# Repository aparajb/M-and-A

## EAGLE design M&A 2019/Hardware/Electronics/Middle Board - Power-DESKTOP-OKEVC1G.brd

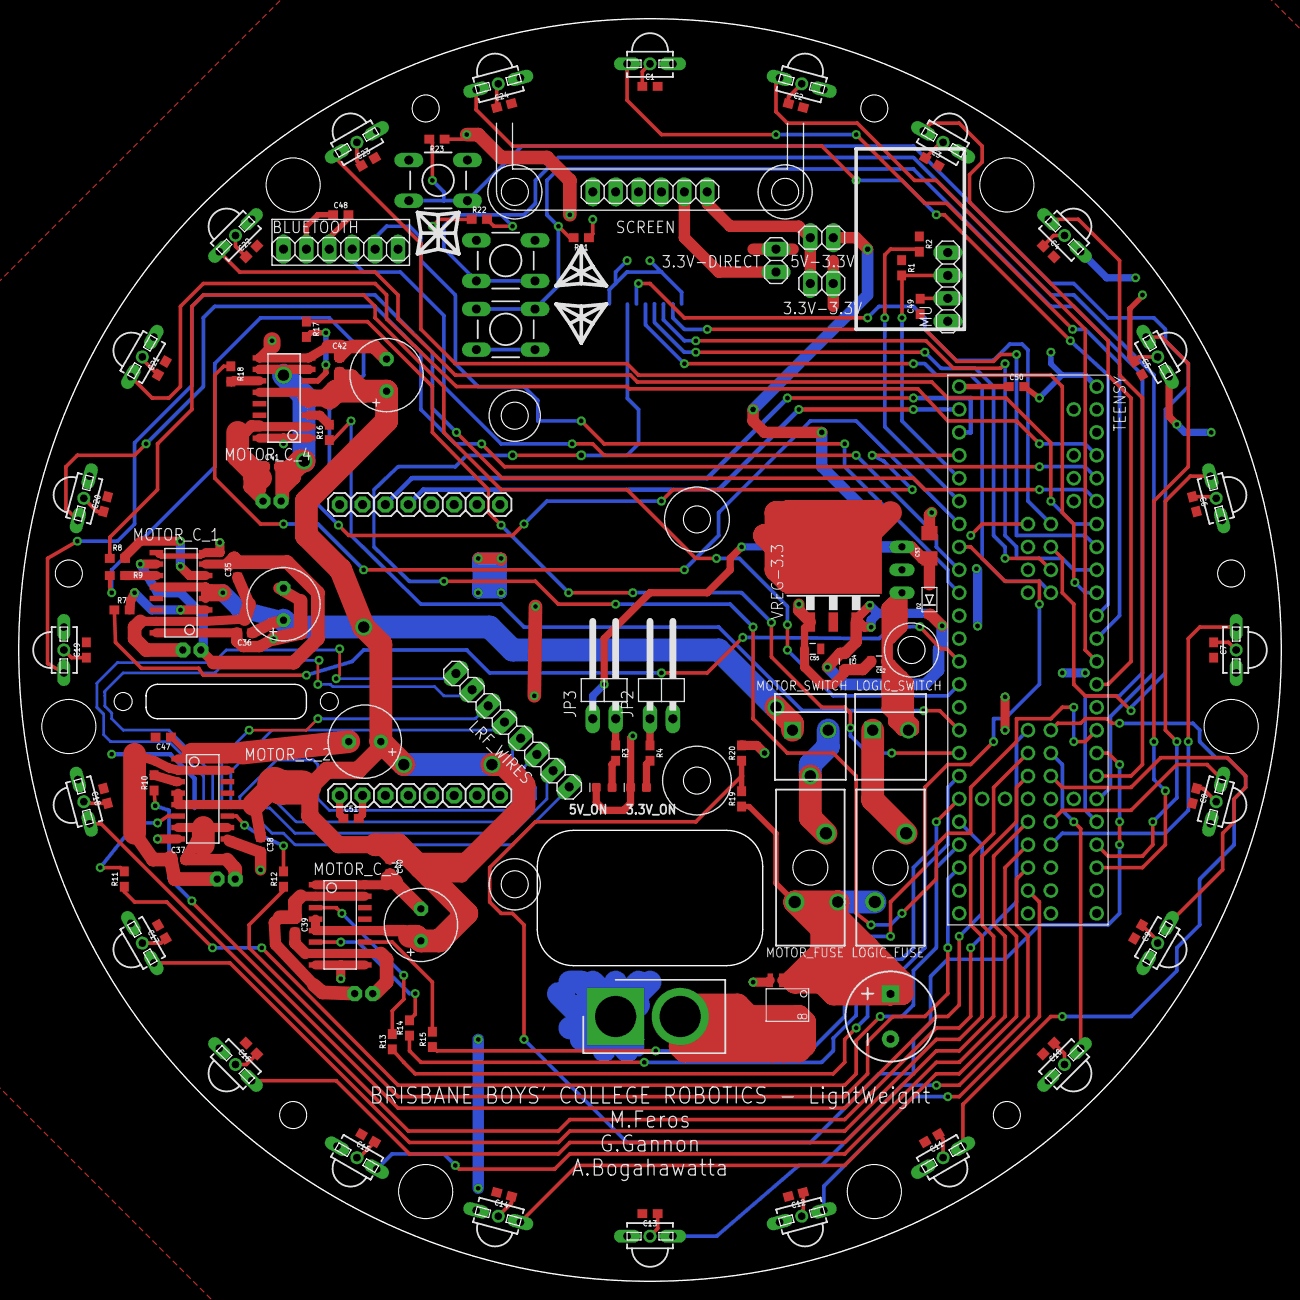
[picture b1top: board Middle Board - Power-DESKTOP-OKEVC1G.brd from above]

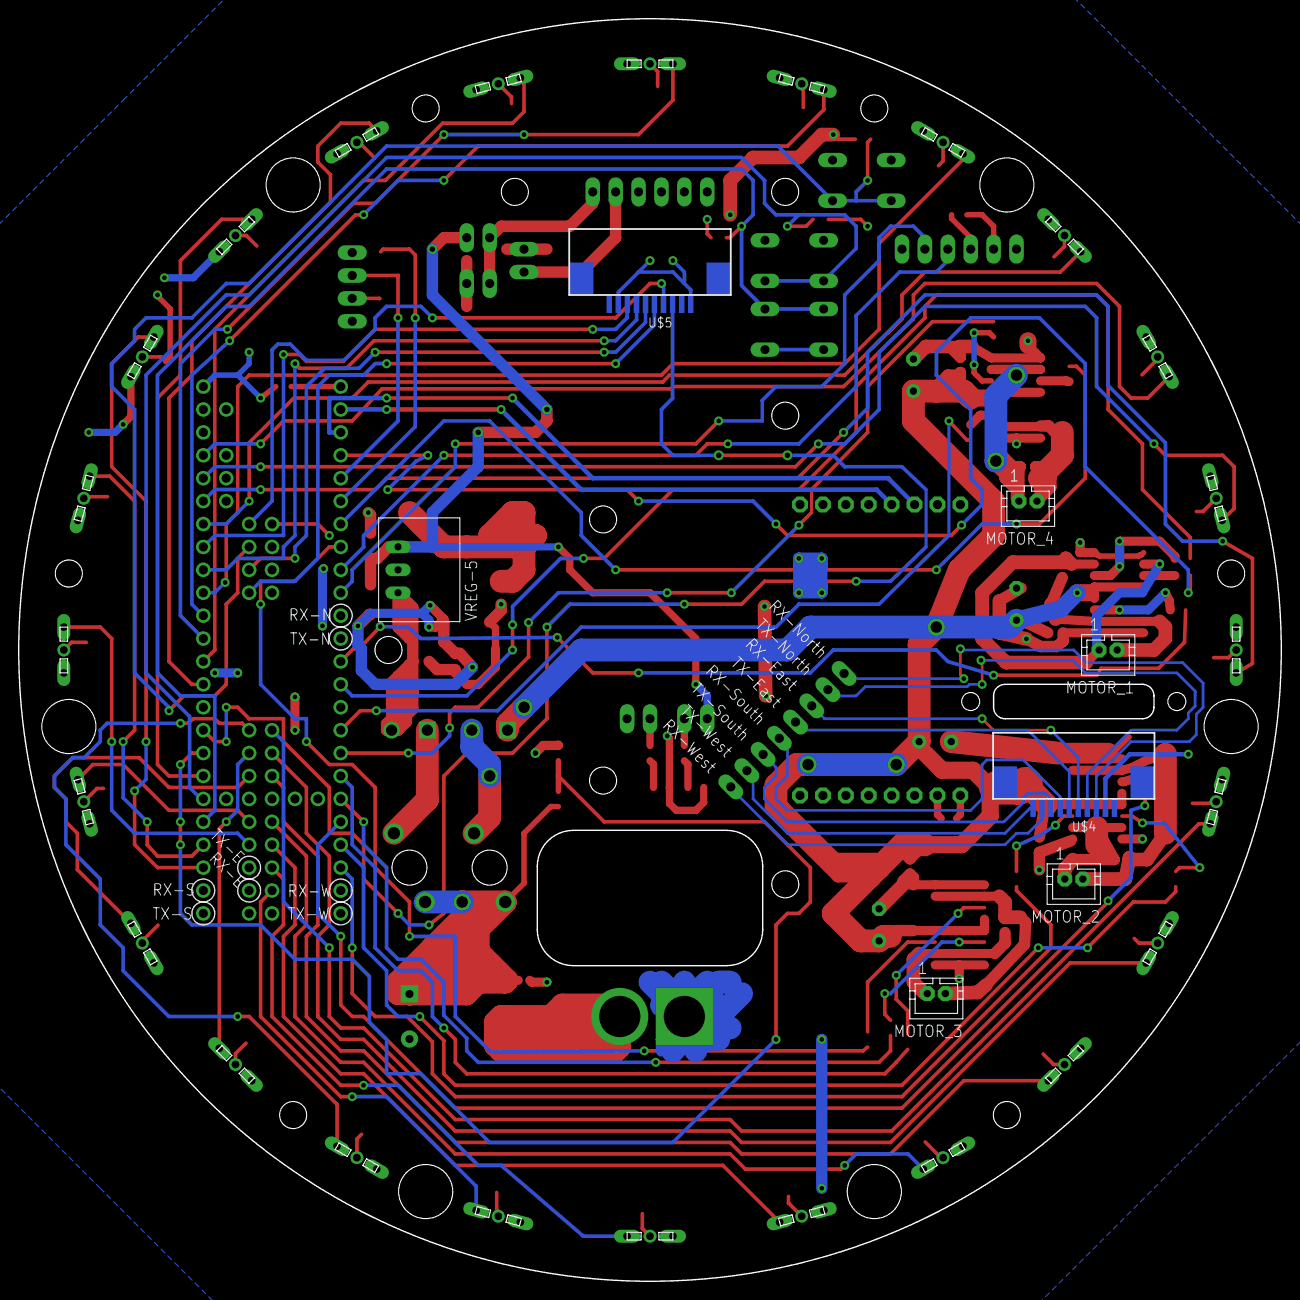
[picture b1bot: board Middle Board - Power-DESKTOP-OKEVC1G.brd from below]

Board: 2 copper layers, 140.0 x 140.0 mm, 126 parts (7 on the bottom side), 96 nets.

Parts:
3.3V-3.3V, 3.3V-DIRECT, 5V-3.3V: 1X02
3.3V_ON, 5V_ON: GREEN; LED-0603
BLUETOOTH: 1X06
C1, C2, C3, C4, C5, C6, C7, C8, C9, C10, C11, C12, C13, C14, C15, C16, C17, C18, C19, C20, C21, C22, C23, C24, C35, C36, C37, C38, C39, C40, C41, C42, C47, C48, C49, C50, C51: 0.1uF; 0603
C25: 1mF; CPOL-RADIAL-5MM-10MM
C43, C44, C45, C46: 470uF; E3,5-8
C52, C54, C55: 10uF; SPARKFUN-CAPACITORS_0805
C53: 22uF; SPARKFUN-CAPACITORS_1206
D2: ADAFRUIT_SOD-123FL
DOWN: DTS-6
IMU: 1X04
J1: PRT-10474; SHDR2W320P716_1X2_1574X813X158
JP2, JP3: 1X02/90
LOGIC_FUSE: FUSE_MINI_BLADE; SL-1538
LOGIC_SWITCH: CONN_02_JST-VH; B2P-VH
LRF_WIRES: 1X08
MOTOR_1, MOTOR_2, MOTOR_3, MOTOR_4: JST-PH2
MOTOR_C_1, MOTOR_C_2, MOTOR_C_3, MOTOR_C_4: VNH7100BASTR; SO-16
MOTOR_FUSE: FUSE_MINI_BLADE; SL-1538
MOTOR_SWITCH: CONN_02_JST-VH; B2P-VH
OPEN-MV: OPENMV3
R1, R2, R21, R22, R23: 10k; 0603
R3, R4: 680; 0603
R7, R8, R9, R10, R11, R12, R13, R14, R15, R16, R17, R18: 1k; 0603
R19: 35.7kOhm; 0603
R20: 10.2kOhm; 0603
SCREEN: 1X06
SELECT: DTS-6
TEENSY: TEENSY-3.5
TSSP1, TSSP2, TSSP3, TSSP4, TSSP5, TSSP6, TSSP7, TSSP8, TSSP9, TSSP10, TSSP11, TSSP12, TSSP13, TSSP14, TSSP15, TSSP16, TSSP17, TSSP18, TSSP19, TSSP20, TSSP21, TSSP22, TSSP23, TSSP24: TSSP58038; MINICAST
U$2: SI4143DY; SO-8
U$4, U$5: FPC10
UP: DTS-6
VREG-3.3: LINEAR_LM340S-05; LINEAR_TO263-3
VREG-5: V78-2000-SWITCHING-REGULATOR_V78-2000

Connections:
3.3V: 3.3V-3.3V.1, 3.3V-DIRECT.1, BLUETOOTH.2, C1.2, C2.2, C3.2, C4.2, C5.2, C6.2, C7.2, C8.2, C9.2, C10.2, C11.2, C12.2, C13.2, C14.2, C15.2, C16.2, C17.2, C18.2, C19.2, C20.2, C21.2, C22.2, C23.2, C24.2, C47.2, C48.1, C49.1, C50.2, C51.2, C55.1, DOWN.1, DOWN.2, IMU.1, JP2.2, OPEN-MV.27, R1.1, R2.1, SELECT.1, SELECT.2, TEENSY.VIN, TSSP1.1, TSSP2.1, TSSP3.1, TSSP4.1, TSSP5.1, TSSP6.1, TSSP7.1, TSSP8.1, TSSP9.1, TSSP10.1, TSSP11.1, TSSP12.1, TSSP13.1, TSSP14.1, TSSP15.1, TSSP16.1, TSSP17.1, TSSP18.1, TSSP19.1, TSSP20.1, TSSP21.1, TSSP22.1, TSSP23.1, TSSP24.1, U$4.2, U$5.1, U$5.9, UP.1, UP.2, VREG-3.3.2, VREG-3.3.TAB
3.3V_ON: JP2.1, R4.1
5V: 5V-3.3V.1, C53.1, D2.A, JP3.1, VREG-5.3
5V-ON: JP3.2, R3.1
12V: C36.1, C38.1, C40.1, C42.1, C43.+, C44.+, C45.+, C46.+, MOTOR_C_1.4, MOTOR_C_1.5, MOTOR_C_1.12, MOTOR_C_2.4, MOTOR_C_2.5, MOTOR_C_2.12, MOTOR_C_3.4, MOTOR_C_3.5, MOTOR_C_3.12, MOTOR_C_4.4, MOTOR_C_4.5, MOTOR_C_4.12, MOTOR_SWITCH.1
BATTERY-VOLTAGE(ANALOG): R19.2, R20.1, TEENSY.DA0
BDOWN: DOWN.3, DOWN.4, R22.2, TEENSY.38
BSELECT: R23.2, SELECT.3, SELECT.4, TEENSY.56
BUP: R21.2, TEENSY.37, UP.3, UP.4
GND: 3.3V_ON.C, 5V_ON.C, BLUETOOTH.3, C1.1, C2.1, C3.1, C4.1, C5.1, C6.1, C7.1, C8.1, C9.1, C10.1, C11.1, C12.1, C13.1, C14.1, C15.1, C16.1, C17.1, C18.1, C19.1, C20.1, C21.1, C22.1, C23.1, C24.1, C25.-, C36.2, C38.2, C40.2, C42.2, C43.-, C44.-, C45.-, C46.-, C47.1, C48.2, C49.2, C50.1, C51.1, C52.2, C53.2, C54.2, C55.2, IMU.2, J1.1, MOTOR_C_1.1, MOTOR_C_1.8, MOTOR_C_1.9, MOTOR_C_1.16, MOTOR_C_2.1, MOTOR_C_2.8, MOTOR_C_2.9, MOTOR_C_2.16, MOTOR_C_3.1, MOTOR_C_3.8, MOTOR_C_3.9, MOTOR_C_3.16, MOTOR_C_4.1, MOTOR_C_4.8, MOTOR_C_4.9, MOTOR_C_4.16, OPEN-MV.28, R20.2, R21.1, R22.1, R23.1, SCREEN.4, TEENSY.GND, TEENSY.GND-2, TEENSY.GND-3, TEENSY.GND-4, TSSP1.2, TSSP2.2, TSSP3.2, TSSP4.2, TSSP5.2, TSSP6.2, TSSP7.2, TSSP8.2, TSSP9.2, TSSP10.2, TSSP11.2, TSSP12.2, TSSP13.2, TSSP14.2, TSSP15.2, TSSP16.2, TSSP17.2, TSSP18.2, TSSP19.2, TSSP20.2, TSSP21.2, TSSP22.2, TSSP23.2, TSSP24.2, U$2.4, U$4.1, U$5.2, U$5.10, VREG-3.3.1, VREG-5.2
LS-CONTROL1: TEENSY.19, U$5.8
LS-CONTROL2: TEENSY.18, U$5.7
LS-CONTROL3: TEENSY.55, U$5.6
LS-CONTROL4: TEENSY.54, U$5.5
LS-CONTROL5: TEENSY.57, U$5.4
LS-OUTPUT: TEENSY.DA1, U$5.3
MOTOR-BL(ENA): R16.1, TEENSY.24
MOTOR-BL(ENB): R17.1, TEENSY.25
MOTOR-BL(PWM): R18.1, TEENSY.5
MOTOR-BR(ENA): R13.1, TEENSY.26
MOTOR-BR(ENB): R14.1, TEENSY.27
MOTOR-BR(PWM): R15.1, TEENSY.6
MOTOR-FL(ENA): R7.1, TEENSY.11
MOTOR-FL(ENB): R8.1, TEENSY.12
MOTOR-FL(PWM): R9.1, TEENSY.2
MOTOR-FR(ENA): R10.1, TEENSY.28
MOTOR-FR(ENB): R11.1, TEENSY.29
MOTOR-FR(PWM): R12.1, TEENSY.30
unnamed: J1.2, U$2.5, U$2.6, U$2.7, U$2.8
unnamed: MOTOR_FUSE.P$2, MOTOR_SWITCH.2
unnamed: C25.+, LOGIC_FUSE.P$1, MOTOR_FUSE.P$1, R19.1, U$2.1, U$2.2, U$2.3
unnamed: LOGIC_FUSE.P$2, LOGIC_SWITCH.1
unnamed: MOTOR_C_1.3, R7.2
unnamed: 5V_ON.A, R3.2
unnamed: 3.3V_ON.A, R4.2
unnamed: MOTOR_C_1.6, R8.2
unnamed: MOTOR_C_1.11, R9.2
unnamed: C35.1, MOTOR_1.2, MOTOR_C_1.2, MOTOR_C_1.15
unnamed: C35.2, MOTOR_1.1, MOTOR_C_1.7, MOTOR_C_1.10
unnamed: MOTOR_C_2.3, R10.2
unnamed: MOTOR_C_2.6, R11.2
unnamed: MOTOR_C_2.11, R12.2
unnamed: C37.1, MOTOR_2.2, MOTOR_C_2.2, MOTOR_C_2.15
unnamed: C37.2, MOTOR_2.1, MOTOR_C_2.7, MOTOR_C_2.10
unnamed: MOTOR_C_3.3, R13.2
unnamed: MOTOR_C_3.6, R14.2
unnamed: MOTOR_C_3.11, R15.2
unnamed: C39.1, MOTOR_3.2, MOTOR_C_3.2, MOTOR_C_3.15
unnamed: C39.2, MOTOR_3.1, MOTOR_C_3.7, MOTOR_C_3.10
unnamed: MOTOR_C_4.3, R16.2
unnamed: MOTOR_C_4.6, R17.2
unnamed: MOTOR_C_4.11, R18.2
unnamed: C41.1, MOTOR_4.2, MOTOR_C_4.2, MOTOR_C_4.15
unnamed: C41.2, MOTOR_4.1, MOTOR_C_4.7, MOTOR_C_4.10
unnamed: 3.3V-DIRECT.2, SCREEN.5
unnamed: 3.3V-3.3V.2, 5V-3.3V.2, SCREEN.6
unnamed: C52.1, LOGIC_SWITCH.2, VREG-5.1
unnamed: C54.1, D2.C, VREG-3.3.3
RX(BLUETOOTH): BLUETOOTH.5, TEENSY.8
RX(CAM): OPEN-MV.16, TEENSY.1
RXE: LRF_WIRES.6, U$4.5
RXN: LRF_WIRES.8, U$4.3
RXS: LRF_WIRES.4, U$4.7
RXW: LRF_WIRES.1, U$4.9
SCL(IMU): IMU.3, R1.2, TEENSY.3
SDA(IMU): IMU.4, R2.2, TEENSY.4
TSSP1: TEENSY.15, TSSP1.3
TSSP2: TEENSY.14, TSSP2.3
TSSP3: TEENSY.13, TSSP3.3
TSSP4: TEENSY.39, TSSP4.3
TSSP5: TEENSY.35, TSSP5.3
TSSP6: TEENSY.36, TSSP6.3
TSSP7: TEENSY.49, TSSP7.3
TSSP8: TEENSY.50, TSSP8.3
TSSP9: TEENSY.51, TSSP9.3
TSSP10: TEENSY.52, TSSP10.3
TSSP11: TEENSY.53, TSSP11.3
TSSP12: TEENSY.46, TSSP12.3
TSSP13: TEENSY.45, TSSP13.3
TSSP14: TEENSY.44, TSSP14.3
TSSP15: TEENSY.43, TSSP15.3
TSSP16: TEENSY.42, TSSP16.3
TSSP17: TEENSY.41, TSSP17.3
TSSP18: TEENSY.40, TSSP18.3
TSSP19: TEENSY.21, TSSP19.3
TSSP20: TEENSY.22, TSSP20.3
TSSP21: TEENSY.23, TSSP21.3
TSSP22: TEENSY.20, TSSP22.3
TSSP23: TEENSY.17, TSSP23.3
TSSP24: TEENSY.16, TSSP24.3
TX(BLUETOOTH): BLUETOOTH.4, TEENSY.7
TX(CAM): OPEN-MV.15, TEENSY.0
TXE: LRF_WIRES.5, U$4.6
TXN: LRF_WIRES.7, U$4.4
TXS: LRF_WIRES.3, U$4.8
TXW: LRF_WIRES.2, U$4.10

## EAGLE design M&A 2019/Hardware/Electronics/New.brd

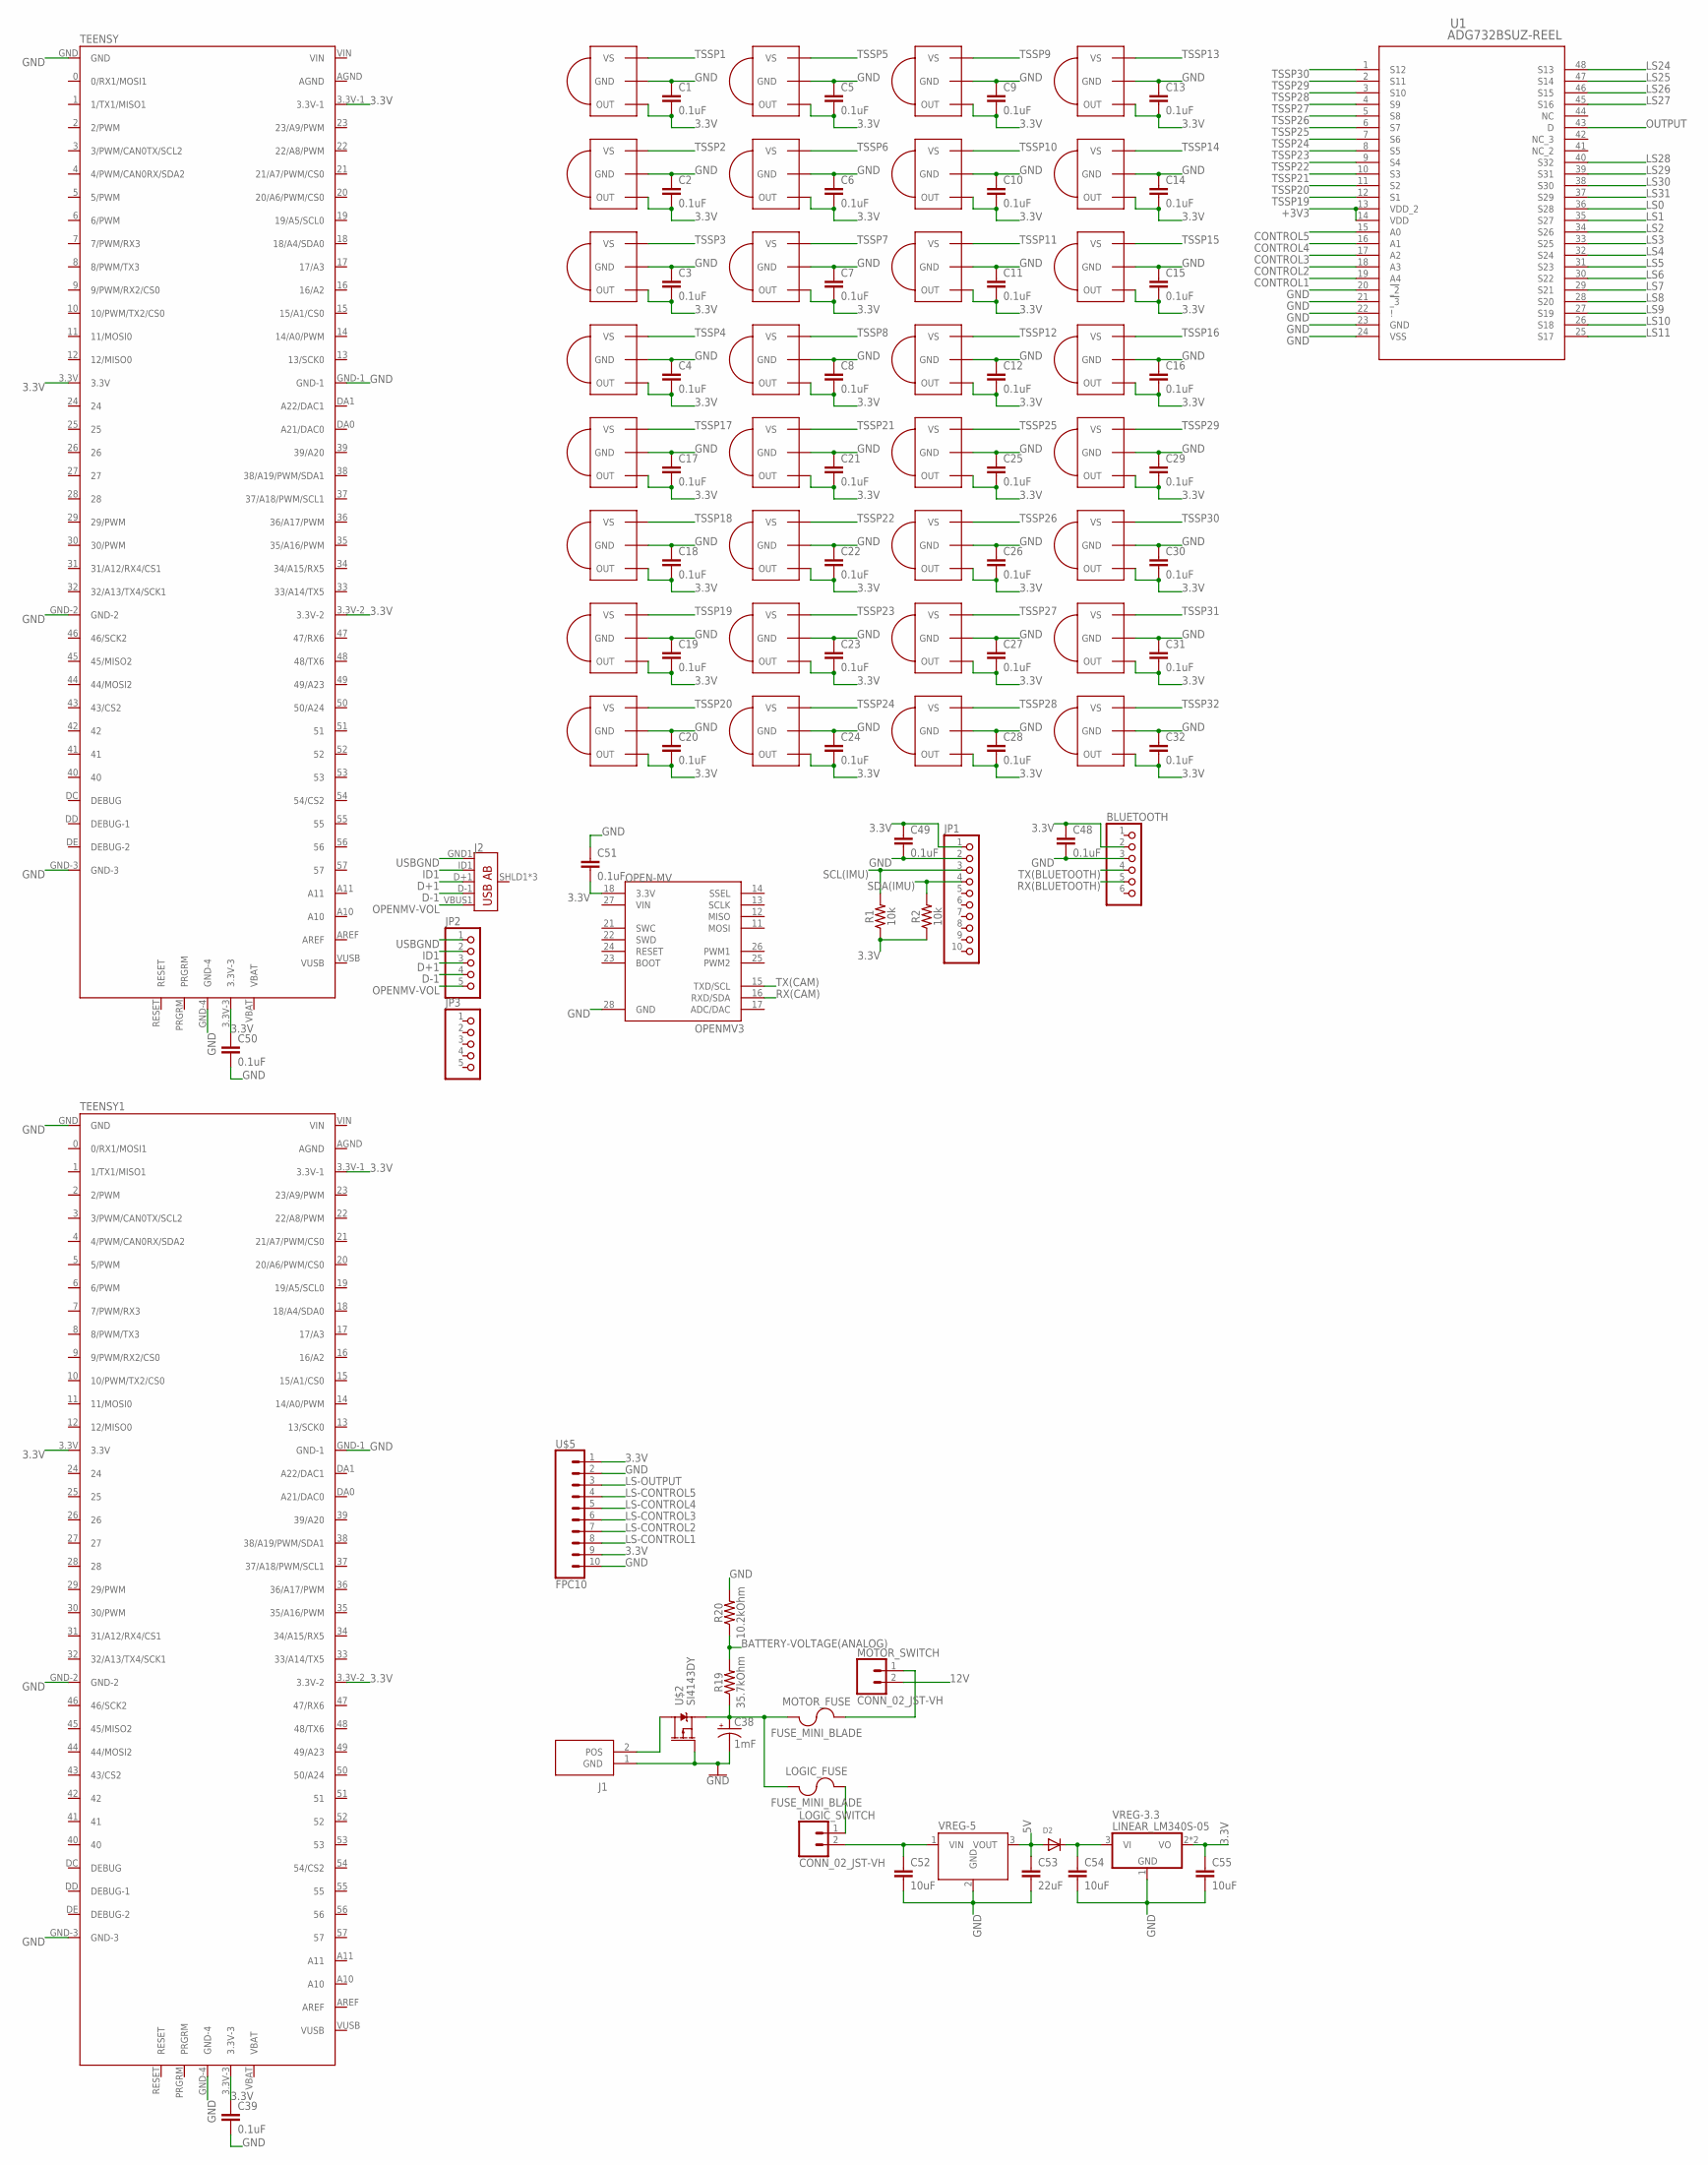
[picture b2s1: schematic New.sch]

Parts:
BLUETOOTH: PINHD-1X6; 1X06
C1, C2, C3, C4, C5, C6, C7, C8, C9, C10, C11, C12, C13, C14, C15, C16, C17, C18, C19, C20, C21, C22, C23, C24, C25, C26, C27, C28, C29, C30, C31, C32, C39, C48, C49, C50, C51: 0.1uF; 0603
C38: 1mF; CPOL-RADIAL-5MM-10MM
C52, C54, C55: 10uF; SPARKFUN-CAPACITORS_0805
C53: 22uF; SPARKFUN-CAPACITORS_1206
D2: ADAFRUIT_DIODE_SOD-123FL:1; ADAFRUIT_SOD-123FL
J1: PRT-10474; SHDR2W320P716_1X2_1574X813X158
J2: USB_AB_SMT; USB-AB-MICRO-SMD
JP1: PINHD-1X10; 1X10
JP2, JP3: PINHD-1X5; 1X05
LOGIC_FUSE: FUSE_MINI_BLADE; SL-1538
LOGIC_SWITCH: CONN_02_JST-VH; B2P-VH@1
MOTOR_FUSE: FUSE_MINI_BLADE; SL-1538
MOTOR_SWITCH: CONN_02_JST-VH; B2P-VH@1
OPEN-MV: OPENMV3
R1, R2: 10k; 0603
R19: 35.7kOhm; 0603
R20: 10.2kOhm; 0603
TEENSY, TEENSY1: TEENSY-3.5
TSSP1, TSSP2, TSSP3, TSSP4, TSSP5, TSSP6, TSSP7, TSSP8, TSSP9, TSSP10, TSSP11, TSSP12, TSSP13, TSSP14, TSSP15, TSSP16, TSSP17, TSSP18, TSSP19, TSSP20, TSSP21, TSSP22, TSSP23, TSSP24, TSSP25, TSSP26, TSSP27, TSSP28, TSSP29, TSSP30, TSSP31, TSSP32: TSSP58038; MINICAST
U1: ADG732BSUZ-REEL; SU_48
U$2: SI4143DY; SO-8
U$5: FPC10
VREG-3.3: LINEAR_LM340S-05; LINEAR_TO263-3
VREG-5: V78-2000-SWITCHING-REGULATOR_V78-2000

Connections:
3.3V: BLUETOOTH.2, C1.2, C2.2, C3.2, C4.2, C5.2, C6.2, C7.2, C8.2, C9.2, C10.2, C11.2, C12.2, C13.2, C14.2, C15.2, C16.2, C17.2, C18.2, C19.2, C20.2, C21.2, C22.2, C23.2, C24.2, C25.2, C26.2, C27.2, C28.2, C29.2, C30.2, C31.2, C32.2, C39.1, C48.1, C49.1, C50.1, C51.2, C55.1, JP1.1, OPEN-MV.18 (3.3V), R1.1, R2.1, TEENSY.3.3V, TEENSY.3.3V-1, TEENSY.3.3V-2, TEENSY.3.3V-3, TEENSY1.3.3V, TEENSY1.3.3V-1, TEENSY1.3.3V-2, TEENSY1.3.3V-3, TSSP1.1 (OUT), TSSP2.1 (OUT), TSSP3.1 (OUT), TSSP4.1 (OUT), TSSP5.1 (OUT), TSSP6.1 (OUT), TSSP7.1 (OUT), TSSP8.1 (OUT), TSSP9.1 (OUT), TSSP10.1 (OUT), TSSP11.1 (OUT), TSSP12.1 (OUT), TSSP13.1 (OUT), TSSP14.1 (OUT), TSSP15.1 (OUT), TSSP16.1 (OUT), TSSP17.1 (OUT), TSSP18.1 (OUT), TSSP19.1 (OUT), TSSP20.1 (OUT), TSSP21.1 (OUT), TSSP22.1 (OUT), TSSP23.1 (OUT), TSSP24.1 (OUT), TSSP25.1 (OUT), TSSP26.1 (OUT), TSSP27.1 (OUT), TSSP28.1 (OUT), TSSP29.1 (OUT), TSSP30.1 (OUT), TSSP31.1 (OUT), TSSP32.1 (OUT), U$5.1, U$5.9, VREG-3.3.2 (VO), VREG-3.3.TAB (VO)
5V: C53.1, D2.A, VREG-5.3 (VOUT)
12V: MOTOR_SWITCH.2
+3V3: U1.13 (VDD_2), U1.14 (VDD)
BATTERY-VOLTAGE(ANALOG): R19.2, R20.1
CONTROL1: U1.19 (A4)
CONTROL2: U1.18 (A3)
CONTROL3: U1.17 (A2)
CONTROL4: U1.16 (A1)
CONTROL5: U1.15 (A0)
D+1: J2.D+1 (D+), JP2.3
D-1: J2.D-1 (D-), JP2.4
GND: BLUETOOTH.3, C1.1, C2.1, C3.1, C4.1, C5.1, C6.1, C7.1, C8.1, C9.1, C10.1, C11.1, C12.1, C13.1, C14.1, C15.1, C16.1, C17.1, C18.1, C19.1, C20.1, C21.1, C22.1, C23.1, C24.1, C25.1, C26.1, C27.1, C28.1, C29.1, C30.1, C31.1, C32.1, C38.-, C39.2, C48.2, C49.2, C50.2, C51.1, C52.2, C53.2, C54.2, C55.2, J1.1 (GND), JP1.2, OPEN-MV.28 (GND), R20.2, TEENSY.GND, TEENSY.GND-1, TEENSY.GND-2, TEENSY.GND-3, TEENSY.GND-4, TEENSY1.GND, TEENSY1.GND-1, TEENSY1.GND-2, TEENSY1.GND-3, TEENSY1.GND-4, TSSP1.2 (GND), TSSP2.2 (GND), TSSP3.2 (GND), TSSP4.2 (GND), TSSP5.2 (GND), TSSP6.2 (GND), TSSP7.2 (GND), TSSP8.2 (GND), TSSP9.2 (GND), TSSP10.2 (GND), TSSP11.2 (GND), TSSP12.2 (GND), TSSP13.2 (GND), TSSP14.2 (GND), TSSP15.2 (GND), TSSP16.2 (GND), TSSP17.2 (GND), TSSP18.2 (GND), TSSP19.2 (GND), TSSP20.2 (GND), TSSP21.2 (GND), TSSP22.2 (GND), TSSP23.2 (GND), TSSP24.2 (GND), TSSP25.2 (GND), TSSP26.2 (GND), TSSP27.2 (GND), TSSP28.2 (GND), TSSP29.2 (GND), TSSP30.2 (GND), TSSP31.2 (GND), TSSP32.2 (GND), U1.20 (!_2), U1.21 (!_3), U1.22 (!), U1.23 (GND), U1.24 (VSS), U$2.4 (G), U$5.2, U$5.10, VREG-3.3.1 (GND), VREG-5.2 (GND)
ID1: J2.ID1 (USBID), JP2.2
LS0: U1.36 (S28)
LS1: U1.35 (S27)
LS2: U1.34 (S26)
LS3: U1.33 (S25)
LS4: U1.32 (S24)
LS5: U1.31 (S23)
LS6: U1.30 (S22)
LS7: U1.29 (S21)
LS8: U1.28 (S20)
LS9: U1.27 (S19)
LS10: U1.26 (S18)
LS11: U1.25 (S17)
LS24: U1.48 (S13)
LS25: U1.47 (S14)
LS26: U1.46 (S15)
LS27: U1.45 (S16)
LS28: U1.40 (S32)
LS29: U1.39 (S31)
LS30: U1.38 (S30)
LS31: U1.37 (S29)
LS-CONTROL1: U$5.8
LS-CONTROL2: U$5.7
LS-CONTROL3: U$5.6
LS-CONTROL4: U$5.5
LS-CONTROL5: U$5.4
LS-OUTPUT: U$5.3
unnamed: J1.2 (POS), U$2.5 (D), U$2.6 (D), U$2.7 (D), U$2.8 (D)
unnamed: MOTOR_FUSE.P$2 (2), MOTOR_SWITCH.1
unnamed: C38.+, LOGIC_FUSE.P$1 (1), MOTOR_FUSE.P$1 (1), R19.1, U$2.1 (S), U$2.2 (S), U$2.3 (S)
unnamed: LOGIC_FUSE.P$2 (2), LOGIC_SWITCH.1
unnamed: C52.1, LOGIC_SWITCH.2, VREG-5.1 (VIN)
unnamed: C54.1, D2.C, VREG-3.3.3 (VI)
OPENMV-VOL: J2.VBUS1 (VBUS), JP2.5
OUTPUT: U1.43 (D)
RX(BLUETOOTH): BLUETOOTH.5
RX(CAM): OPEN-MV.16 (RXD/SDA)
SCL(IMU): JP1.3, R1.2
SDA(IMU): JP1.4, R2.2
TSSP1: TSSP1.3 (VS)
TSSP2: TSSP2.3 (VS)
TSSP3: TSSP3.3 (VS)
TSSP4: TSSP4.3 (VS)
TSSP5: TSSP5.3 (VS)
TSSP6: TSSP6.3 (VS)
TSSP7: TSSP7.3 (VS)
TSSP8: TSSP8.3 (VS)
TSSP9: TSSP9.3 (VS)
TSSP10: TSSP10.3 (VS)
TSSP11: TSSP11.3 (VS)
TSSP12: TSSP12.3 (VS)
TSSP13: TSSP13.3 (VS)
TSSP14: TSSP14.3 (VS)
TSSP15: TSSP15.3 (VS)
TSSP16: TSSP16.3 (VS)
TSSP17: TSSP17.3 (VS)
TSSP18: TSSP18.3 (VS)
TSSP19: TSSP19.3 (VS), U1.12 (S1)
TSSP20: TSSP20.3 (VS), U1.11 (S2)
TSSP21: TSSP21.3 (VS), U1.10 (S3)
TSSP22: TSSP22.3 (VS), U1.9 (S4)
TSSP23: TSSP23.3 (VS), U1.8 (S5)
TSSP24: TSSP24.3 (VS), U1.7 (S6)
TSSP25: TSSP25.3 (VS), U1.6 (S7)
TSSP26: TSSP26.3 (VS), U1.5 (S8)
TSSP27: TSSP27.3 (VS), U1.4 (S9)
TSSP28: TSSP28.3 (VS), U1.3 (S10)
TSSP29: TSSP29.3 (VS), U1.2 (S11)
TSSP30: TSSP30.3 (VS), U1.1 (S12)
TSSP31: TSSP31.3 (VS)
TSSP32: TSSP32.3 (VS)
TX(BLUETOOTH): BLUETOOTH.4
TX(CAM): OPEN-MV.15 (TXD/SCL)
USBGND: J2.GND1 (GND), JP2.1
VIN: OPEN-MV.27 (VIN)

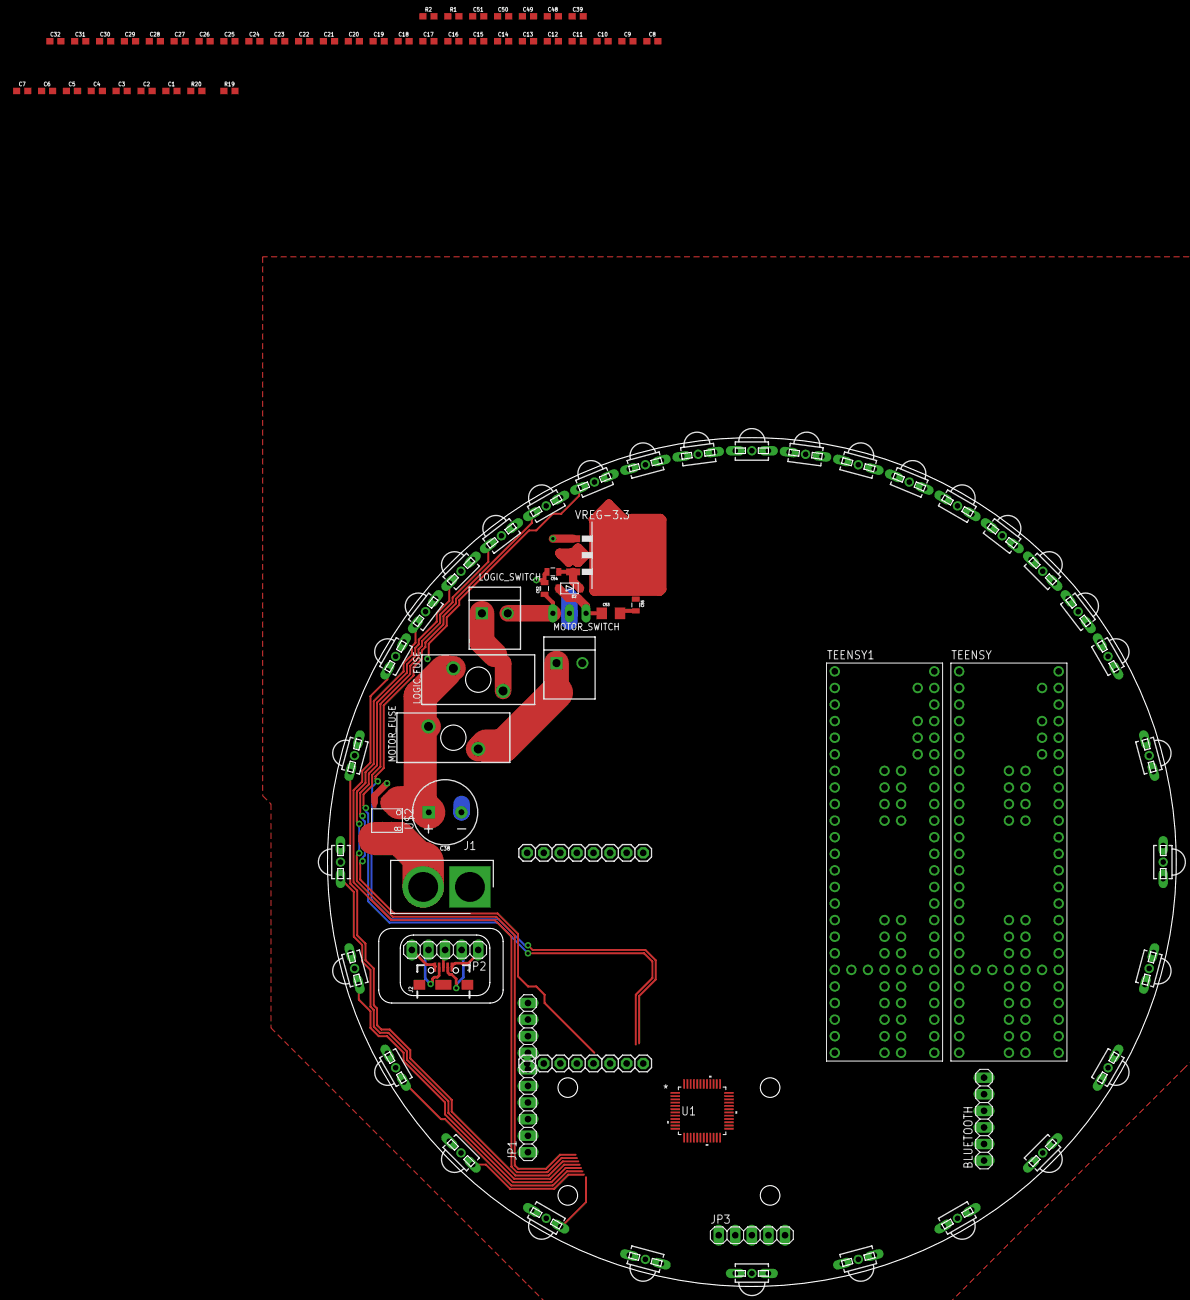
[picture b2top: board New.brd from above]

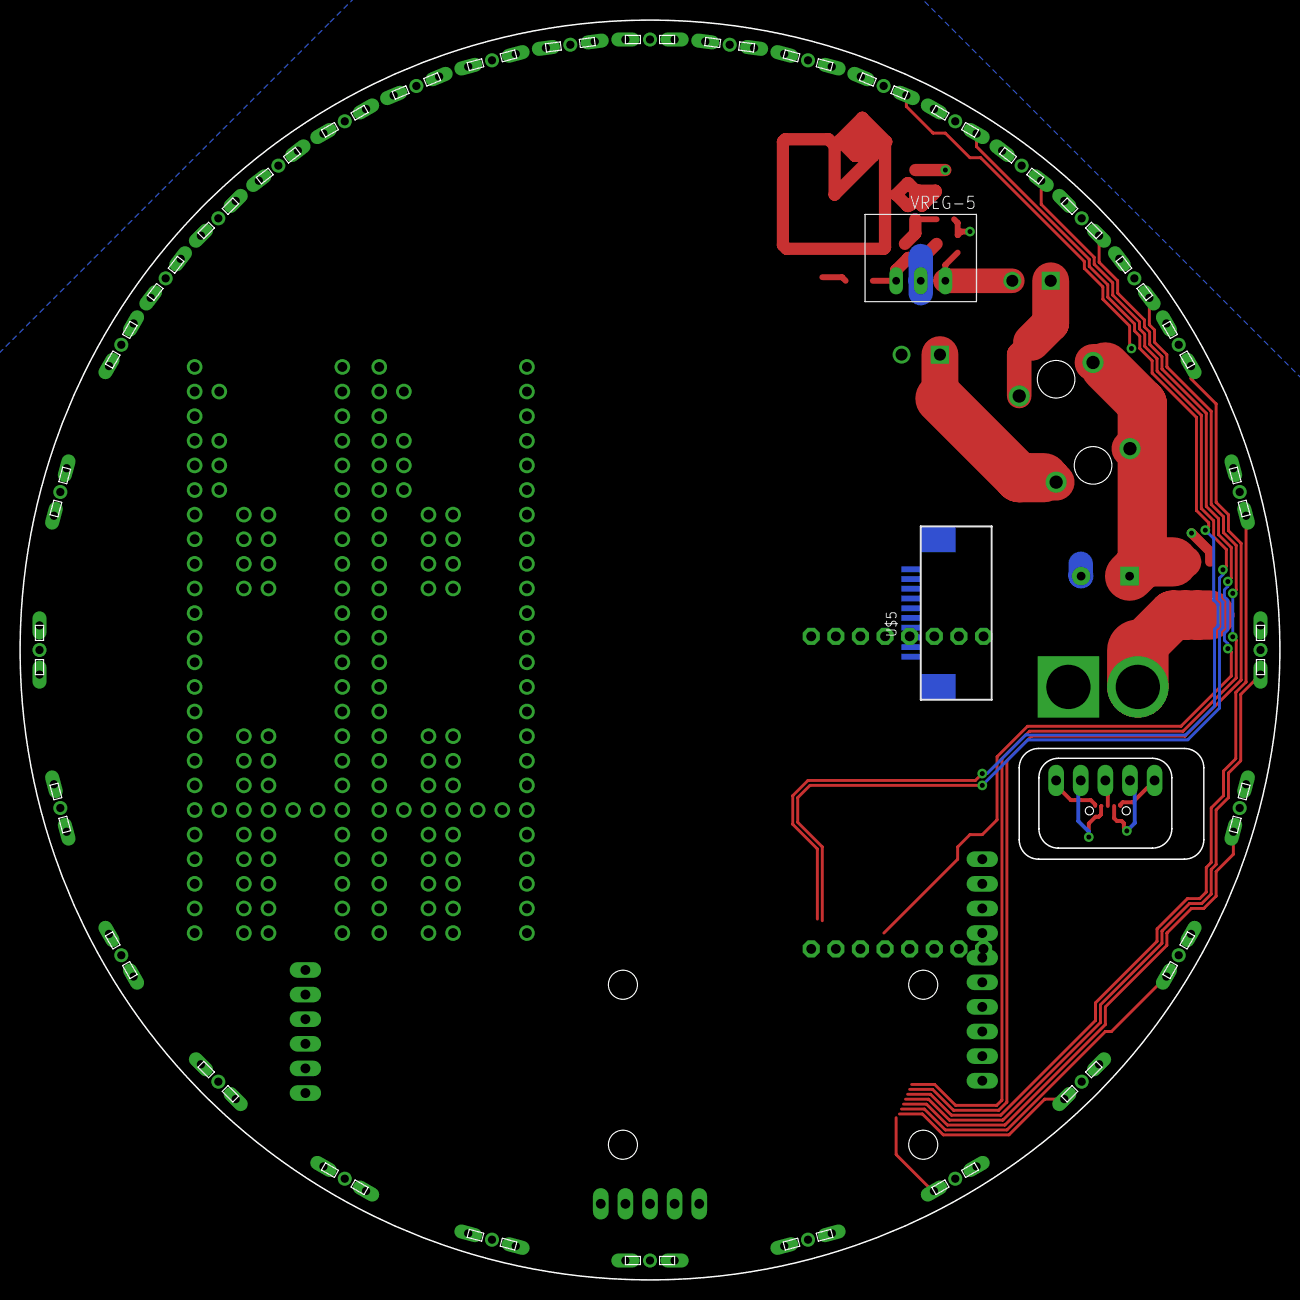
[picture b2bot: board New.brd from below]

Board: 2 copper layers, 130.0 x 130.0 mm, 97 parts (2 on the bottom side), 30 nets.

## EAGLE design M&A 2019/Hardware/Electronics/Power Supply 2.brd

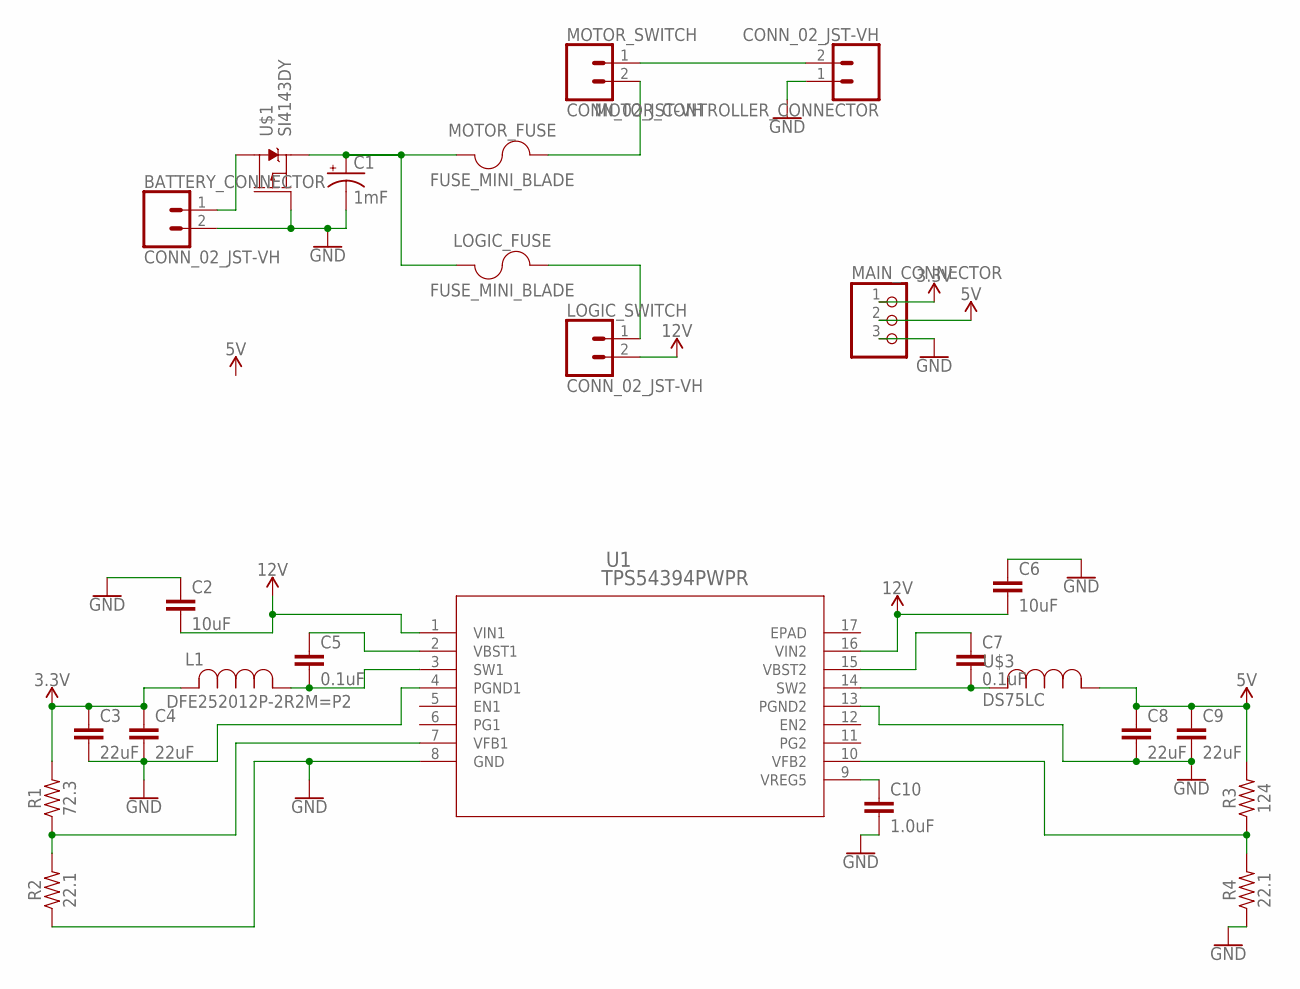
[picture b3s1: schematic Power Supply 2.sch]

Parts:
BATTERY_CONNECTOR: CONN_02_JST-VH; B2P-VH
C1: 1mF; CPOL-RADIAL-5MM-10MM
C2, C6: 10uF; 0805
C3, C4, C8, C9: 22uF; 0805
C5, C7: 0.1uF; 0603
C10: 1.0uF; 0805
L1: DFE252012P-2R2M=P2; DFE252012P-1R0M=P2
LOGIC_FUSE: FUSE_MINI_BLADE; SL-1538
LOGIC_SWITCH: CONN_02_JST-VH; B2P-VH
MAIN_CONNECTOR: PINHD-1X3; 1X03
MOTOR_CONTROLLER_CONNECTOR: CONN_02_JST-VH; B2P-VH
MOTOR_FUSE: FUSE_MINI_BLADE; SL-1538
MOTOR_SWITCH: CONN_02_JST-VH; B2P-VH
R1: 72.3; 0603
R2, R4: 22.1; 0603
R3: 124; 0603
U1: TPS54394PWPR; PWP16_3P4X2P46
U$1: SI4143DY; SO-8
U$3: DS75LC

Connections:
3.3V: C3.1, C4.1, L1.2, MAIN_CONNECTOR.1, R1.2
5V: C8.1, C9.1, MAIN_CONNECTOR.2, R3.2, U$3.P$1 (1)
12V: C2.2, C6.2, LOGIC_SWITCH.2, U1.1 (VIN1), U1.16 (VIN2)
GND: BATTERY_CONNECTOR.2, C1.-, C2.1, C3.2, C4.2, C6.1, C8.2, C9.2, C10.2, MAIN_CONNECTOR.3, MOTOR_CONTROLLER_CONNECTOR.1, R2.1, R4.1, U1.4 (PGND1), U1.8 (GND), U1.13 (PGND2), U$1.4 (G)
unnamed: BATTERY_CONNECTOR.1, U$1.5 (D), U$1.6 (D), U$1.7 (D), U$1.8 (D)
unnamed: MOTOR_FUSE.P$2 (2), MOTOR_SWITCH.2
unnamed: C1.+, LOGIC_FUSE.P$1 (1), MOTOR_FUSE.P$1 (1), U$1.1 (S), U$1.2 (S), U$1.3 (S)
unnamed: LOGIC_FUSE.P$2 (2), LOGIC_SWITCH.1
unnamed: MOTOR_CONTROLLER_CONNECTOR.2, MOTOR_SWITCH.1
unnamed: C5.1, U1.2 (VBST1)
unnamed: C5.2, L1.1, U1.3 (SW1)
unnamed: C7.1, U1.15 (VBST2)
unnamed: R1.1, R2.2, U1.7 (VFB1)
unnamed: C7.2, U1.14 (SW2), U$3.P$2 (2)
unnamed: C10.1, U1.9 (VREG5)
unnamed: R3.1, R4.2, U1.10 (VFB2)

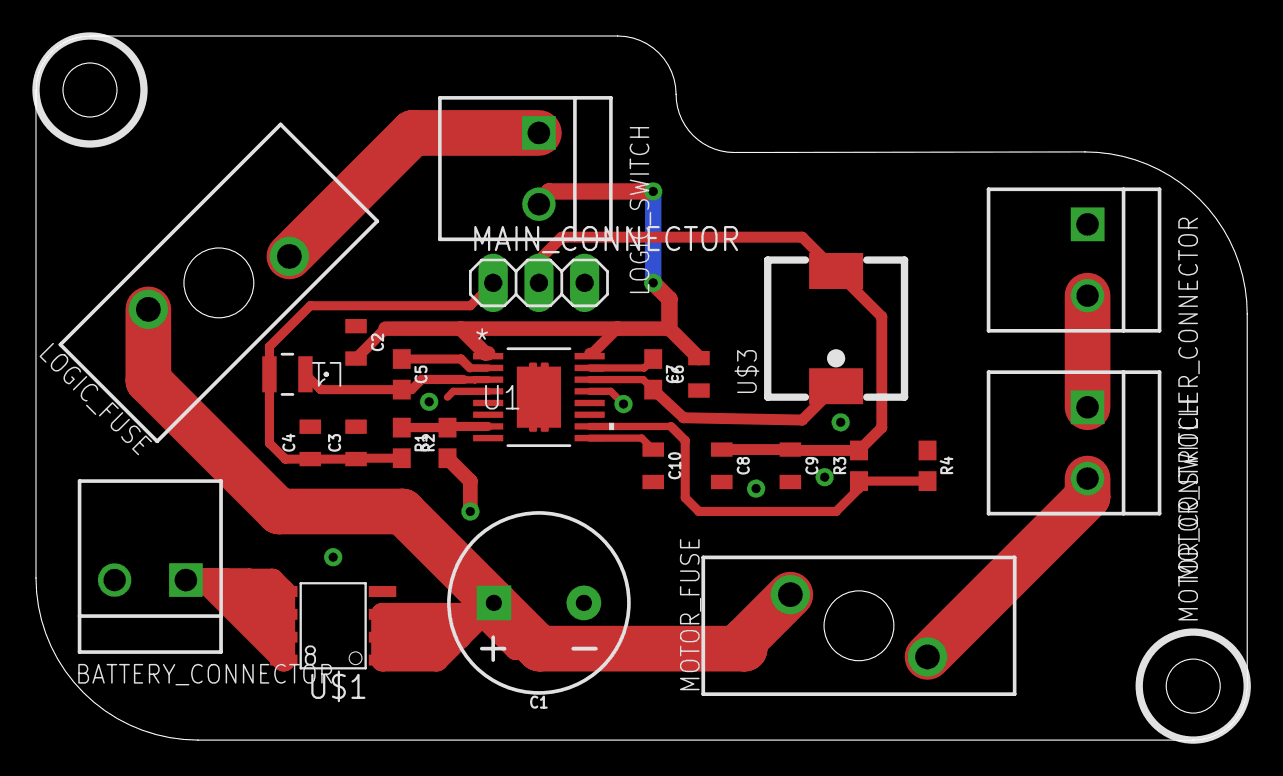
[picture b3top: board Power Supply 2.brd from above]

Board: 2 copper layers, 67.3 x 39.1 mm, 25 parts (0 on the bottom side), 16 nets.

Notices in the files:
parts and their libraries:
SparkFun-Capacitors: Licensing: Creative Commons ShareAlike 4.0 International - https://creativecommons.org/licenses/by-sa/4.0
